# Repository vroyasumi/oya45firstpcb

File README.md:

# oya45firstpcb
 My first try at a PCB

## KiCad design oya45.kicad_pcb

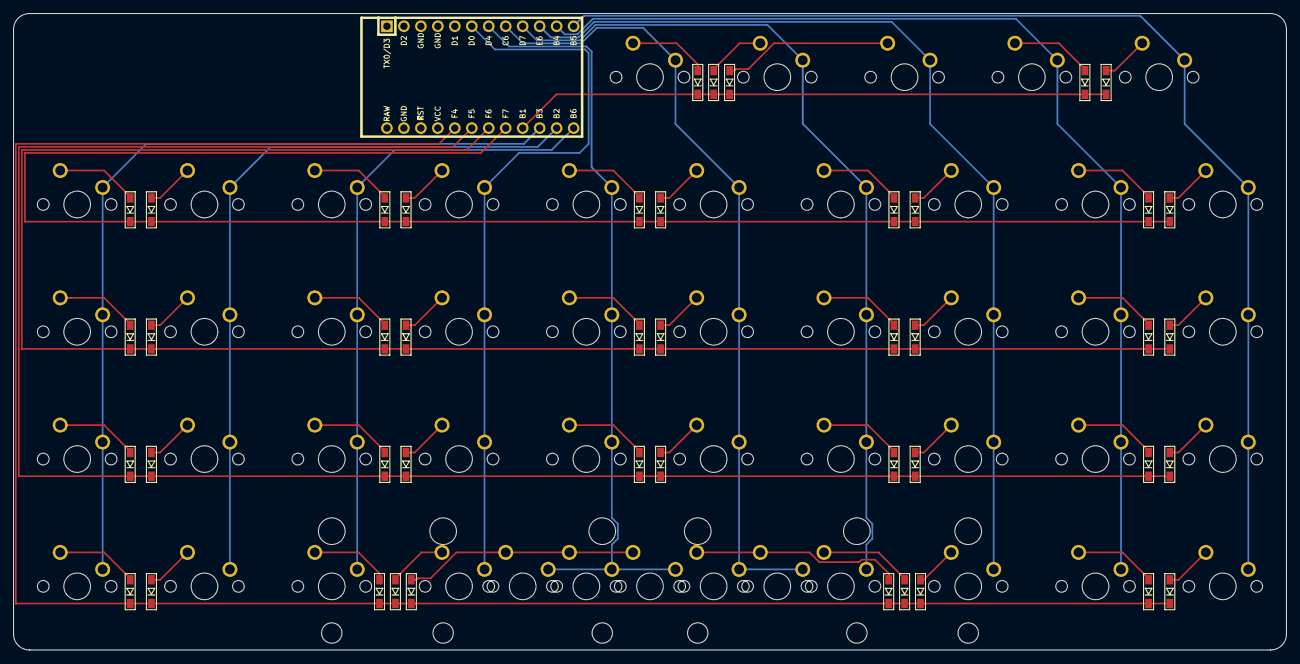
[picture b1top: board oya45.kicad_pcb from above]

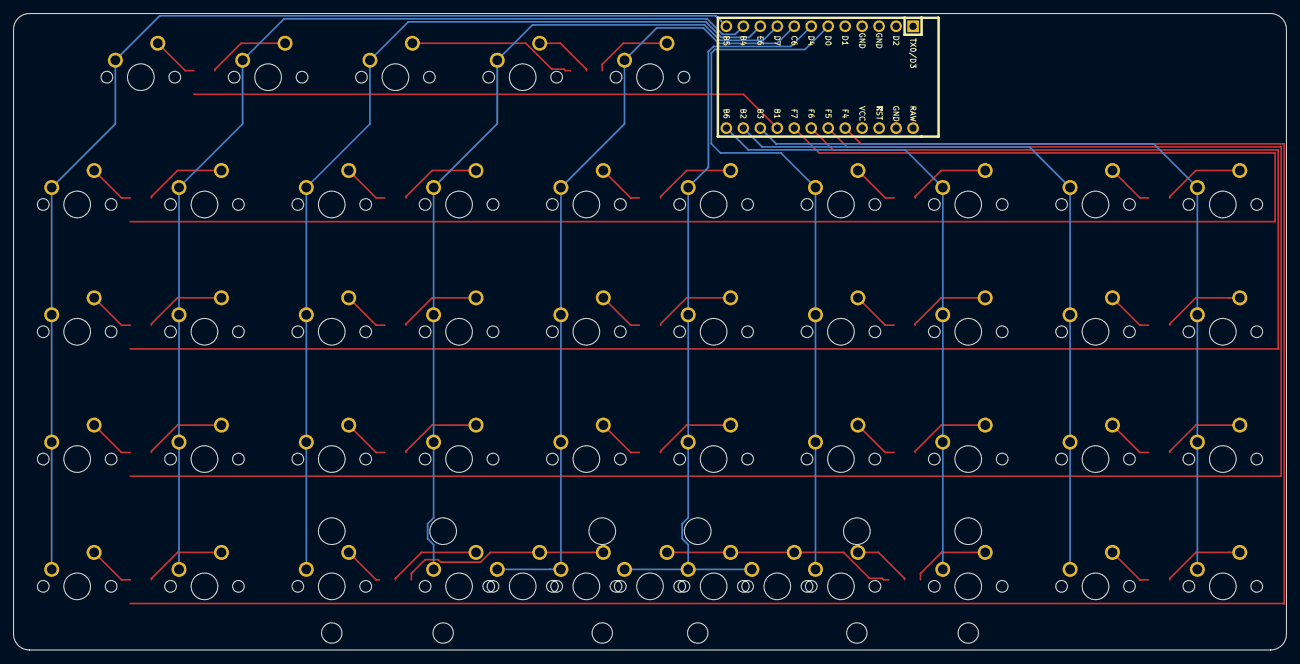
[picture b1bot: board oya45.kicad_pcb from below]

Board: 2 copper layers, 190.5 x 95.2 mm, 94 parts (49 on the bottom side), 60 nets.

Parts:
D1, D2, D3, D4, D5, D6, D7, D8, D9, D10, D11, D12, D13, D14, D15, D16, D17, D18, D19, D20, D21, D22, D23, D24, D25, D26, D27, D28, D29, D30, D31, D32, D33, D34, D35, D36, D37, D38, D39, D40, D41, D42, D43, D44, D45: D_Small; D3_SMD_v2
MX1, MX2, MX3, MX4, MX5, MX6, MX7, MX8, MX9, MX10, MX11, MX12, MX13, MX14, MX15, MX16, MX17, MX18, MX19, MX20, MX21, MX22, MX23, MX24, MX25, MX26, MX27, MX28, MX29, MX30, MX31, MX32, MX33, MX34, MX35, MX36, MX37, MX38, MX39, MX40, MX41, MX42, MX43, MX44, MX45: MX-NoLED; MXOnly-1U-NoLED
MX46: MX-NoLED; MXOnly-6U-Centered-ReversedStabilizers-NoLED
MX47, MX48: MX-NoLED; MXOnly-2U-ReversedStabilizers-NoLED
U1: ProMicro; ArduinoProMicro

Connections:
unnamed: D1.2, MX1.2
unnamed: D2.2, MX2.2
unnamed: D3.2, MX3.2
unnamed: D4.2, MX4.2
unnamed: D5.2, MX5.2
unnamed: D6.2, MX6.2
unnamed: D7.2, MX7.2
unnamed: D8.2, MX8.2
unnamed: D9.2, MX9.2
unnamed: D10.2, MX10.2
unnamed: D11.2, MX11.2
unnamed: D12.2, MX12.2
unnamed: D13.2, MX13.2
unnamed: D14.2, MX14.2
unnamed: D15.2, MX15.2
unnamed: D16.2, MX16.2
unnamed: D17.2, MX17.2
unnamed: D18.2, MX18.2
unnamed: D19.2, MX19.2
unnamed: D20.2, MX20.2
unnamed: D21.2, MX21.2
unnamed: D22.2, MX22.2
unnamed: D23.2, MX23.2
unnamed: D24.2, MX24.2
unnamed: D25.2, MX25.2
unnamed: D26.2, MX26.2
unnamed: D27.2, MX27.2
unnamed: D28.2, MX28.2
unnamed: D29.2, MX29.2
unnamed: D30.2, MX30.2
unnamed: D31.2, MX31.2
unnamed: D32.2, MX32.2
unnamed: D33.2, MX33.2
unnamed: D34.2, MX34.2
unnamed: D35.2, MX35.2, MX46.2, MX47.2
unnamed: D36.2, MX36.2, MX48.2
unnamed: D37.2, MX37.2
unnamed: D38.2, MX38.2
unnamed: D39.2, MX39.2
unnamed: D40.2, MX40.2
unnamed: D41.2, MX41.2
unnamed: D42.2, MX42.2
unnamed: D43.2, MX43.2
unnamed: D44.2, MX44.2
unnamed: D45.2, MX45.2
col0: MX1.1, MX11.1, MX21.1, MX31.1, U1.15
col1: MX2.1, MX12.1, MX22.1, MX32.1, U1.14
col2: MX3.1, MX13.1, MX23.1, MX33.1, U1.13
col3: MX4.1, MX14.1, MX24.1, MX34.1, U1.6
col4: MX5.1, MX15.1, MX25.1, MX35.1, MX46.1, MX47.1, U1.7
col5: MX6.1, MX16.1, MX26.1, MX36.1, MX41.1, MX48.1, U1.8
col6: MX7.1, MX17.1, MX27.1, MX37.1, MX42.1, U1.9
col7: MX8.1, MX18.1, MX28.1, MX38.1, MX43.1, U1.10
col8: MX9.1, MX19.1, MX29.1, MX39.1, MX44.1, U1.11
col9: MX10.1, MX20.1, MX30.1, MX40.1, MX45.1, U1.12
row0: D41.1, D42.1, D43.1, D44.1, D45.1, U1.16
row1: D1.1, D2.1, D3.1, D4.1, D5.1, D6.1, D7.1, D8.1, D9.1, D10.1, U1.17
row2: D11.1, D12.1, D13.1, D14.1, D15.1, D16.1, D17.1, D18.1, D19.1, D20.1, U1.18
row3: D21.1, D22.1, D23.1, D24.1, D25.1, D26.1, D27.1, D28.1, D29.1, D30.1, U1.19
row4: D31.1, D32.1, D33.1, D34.1, D35.1, D36.1, D37.1, D38.1, D39.1, D40.1, U1.20

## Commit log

2021-08-29 Initialize project
2021-08-29 Add submodules
2021-08-29 Add footprint libraries
2021-08-29 Schematics finished
2021-08-29 Schematics finished final
    fixed duplicates
2021-08-29 schematic labeling
2021-08-29 pcb mx placement
2021-08-29 diodes lined up
2021-08-29 less pads
    made a basic pcb instead of complex to make it cheaper
2021-08-29 diodes finished
2021-08-29 save
2021-08-30 added pro micro
    pro micro instead of elite c for less pads
2021-08-30 added fillets
2021-08-30 column tracing
2021-08-30 diode orientation fix
    flipped the diodes because they were facing in a less convenient way
2021-08-30 column and row tracing finished
2021-08-30 col, row, and diode tracing finished
2021-08-30 col, row, and diode tracing finished
    fixed missing col
2021-08-30 route final fixed; first route
    first route, could route cleaner
2021-08-30 pro micro first clean routing
2021-08-30 cleaned col and row with first clean routing
2021-08-30 created gerbers and fixed routing
2021-08-30 added foostan github
2021-08-30 added m2 mounting holes
2021-08-30 added mounting holes
    will have to create plate and bottom plate later. Still deciding how I should mount and what mount points/hole design I should use.
2021-08-31 diode > smd
2021-08-31 much more cleaner tracing
2021-08-31 fixed orientation of pcb
2021-08-31 fixed schematics
    fixed schematics after pcb orientation fix
2021-08-31 fixed schematics
    fixed schematics with orientation of pcb
2021-08-31 fixed schematics
    fixed diode row
2021-08-31 pcb final
2021-08-31 created oya45firstpcbgerbers
2021-08-31 fixed corners of pcb
    bottom corners were the back layer while the top were on the front layer
2021-08-31 fixed pcb corner and edge
    moved pcb edge from back to front
2021-08-31 fixed tracing
    col3 trace fixed
2021-09-01 cleaned up tracing more
    front and back
2021-09-01 final tracing
2021-09-01 finished routing
    fix 1 diode and cleaned up bottom row
2021-09-01 fixed tracing
    fixed bottom row tracing and one diode
2021-09-01 final pcb and created final gerbers
2021-09-01 fixed diode row tracing
2021-09-01 added edge cuts
    used front silk by accident instead of edge cut lines
2021-09-01 cleaned up pcb for final
2021-09-01 final gerbers
2021-09-01 different diode placement
2021-09-02 absolute final
